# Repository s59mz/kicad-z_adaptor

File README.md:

# z_adaptor
Adaptor from Z-Turn I/O Expansion card to several Alinx DAC/ADC, HDMI, Ethernet modules and PMODS

Schematic:
[z_adaptor.pdf](z_adaptor.pdf)

BOM:
[z_adaptor.csv](z_adaptor.csv)

Gerbers:
[gerbers.zip](https://github.com/s59mz/kicad-z_adaptor/raw/main/gerbers.zip)

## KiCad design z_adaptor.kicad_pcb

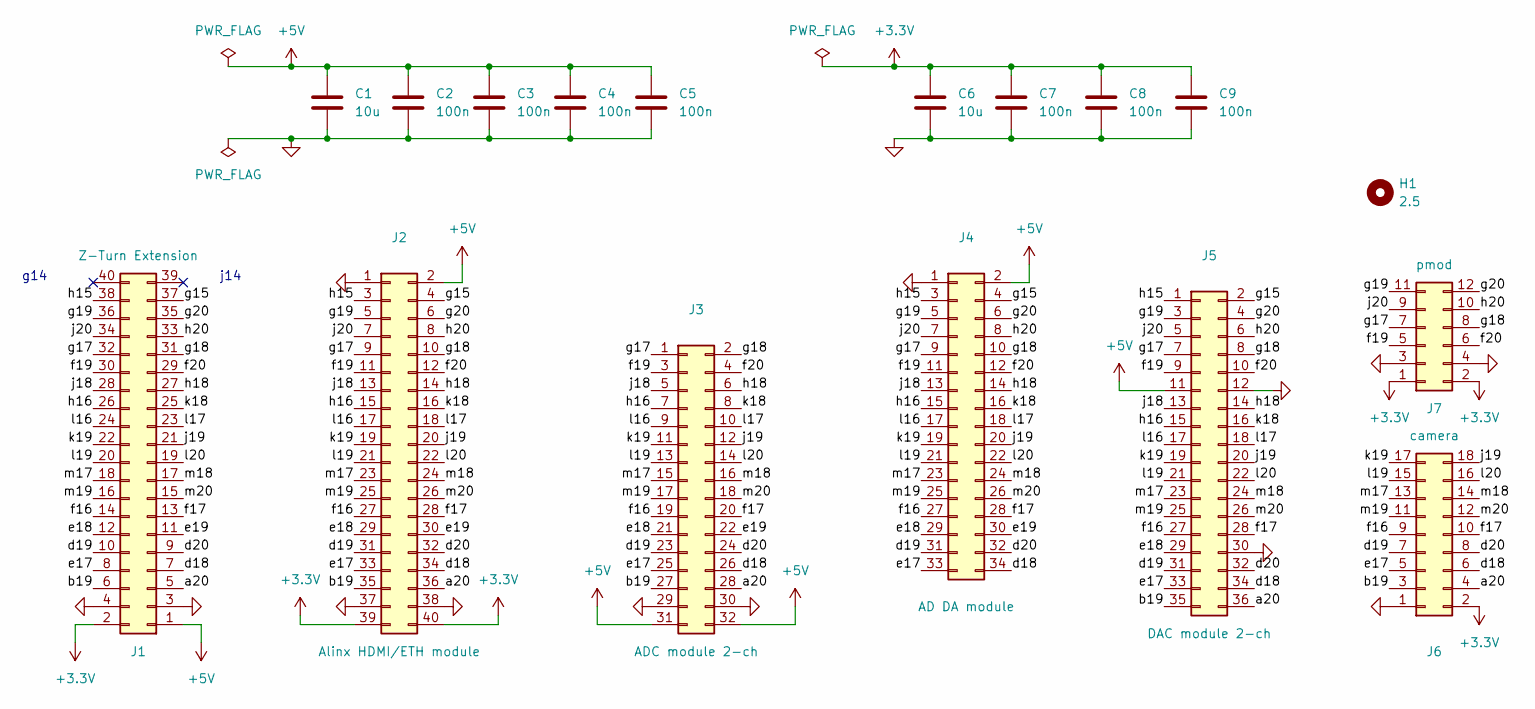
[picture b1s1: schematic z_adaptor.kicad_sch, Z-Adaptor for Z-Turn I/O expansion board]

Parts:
C1, C6: 10u; C_0603_1608Metric_Pad1.08x0.95mm_HandSolder
C2, C3, C4, C5, C7, C8, C9: 100n; C_0603_1608Metric_Pad1.08x0.95mm_HandSolder
H1: 2.5; MountingHole_2.5mm
J1: Z-Turn Extension; PinSocket_2x20_P2.54mm_Vertical
J2: Alinx HDMI/ETH module; PinHeader_2x20_P2.54mm_Vertical
J3: ADC module 2-ch; PinHeader_2x16_P2.54mm_Vertical
J4: AD DA module; PinHeader_2x17_P2.54mm_Vertical
J5: DAC module 2-ch; PinHeader_2x18_P2.54mm_Vertical
J6: camera; PinSocket_2x09_P2.54mm_Horizontal
J7: pmod; PinSocket_2x06_P2.54mm_Horizontal

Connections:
+3.3V: C6.1, C7.1, C8.1, C9.1, J1.2, J2.39, J2.40, J6.2, J7.1, J7.2
+5V: C1.1, C2.1, C3.1, C4.1, C5.1, J1.1, J2.2, J3.31, J3.32, J4.2, J5.11
/a20: J1.5, J2.36, J3.28, J5.36, J6.4
/b19: J1.6, J2.35, J3.27, J5.35, J6.3
/d18: J1.7, J2.34, J3.26, J4.34, J5.34, J6.6
/d19: J1.10, J2.31, J3.23, J4.31, J5.31, J6.7
/d20: J1.9, J2.32, J3.24, J4.32, J5.32, J6.8
/e17: J1.8, J2.33, J3.25, J4.33, J5.33, J6.5
/e18: J1.12, J2.29, J3.21, J4.29, J5.29
/e19: J1.11, J2.30, J3.22, J4.30
/f16: J1.14, J2.27, J3.19, J4.27, J5.27, J6.9
/f17: J1.13, J2.28, J3.20, J4.28, J5.28, J6.10
/f19: J1.30, J2.11, J3.3, J4.11, J5.9, J7.5
/f20: J1.29, J2.12, J3.4, J4.12, J5.10, J7.6
/g15: J1.37, J2.4, J4.4, J5.2
/g17: J1.32, J2.9, J3.1, J4.9, J5.7, J7.7
/g18: J1.31, J2.10, J3.2, J4.10, J5.8, J7.8
/g19: J1.36, J2.5, J4.5, J5.3, J7.11
/g20: J1.35, J2.6, J4.6, J5.4, J7.12
/h15: J1.38, J2.3, J4.3, J5.1
/h16: J1.26, J2.15, J3.7, J4.15, J5.15
/h18: J1.27, J2.14, J3.6, J4.14, J5.14
/h20: J1.33, J2.8, J4.8, J5.6, J7.10
/j18: J1.28, J2.13, J3.5, J4.13, J5.13
/j19: J1.21, J2.20, J3.12, J4.20, J5.20, J6.18
/j20: J1.34, J2.7, J4.7, J5.5, J7.9
/k18: J1.25, J2.16, J3.8, J4.16, J5.16
/k19: J1.22, J2.19, J3.11, J4.19, J5.19, J6.17
/l16: J1.24, J2.17, J3.9, J4.17, J5.17
/l17: J1.23, J2.18, J3.10, J4.18, J5.18
/l19: J1.20, J2.21, J3.13, J4.21, J5.21, J6.15
/l20: J1.19, J2.22, J3.14, J4.22, J5.22, J6.16
/m17: J1.18, J2.23, J3.15, J4.23, J5.23, J6.13
/m18: J1.17, J2.24, J3.16, J4.24, J5.24, J6.14
/m19: J1.16, J2.25, J3.17, J4.25, J5.25, J6.11
/m20: J1.15, J2.26, J3.18, J4.26, J5.26, J6.12
GND: C1.2, C2.2, C3.2, C4.2, C5.2, C6.2, C7.2, C8.2, C9.2, J1.3, J1.4, J2.1, J2.37, J2.38, J3.29, J3.30, J4.1, J5.12, J5.30, J6.1, J7.3, J7.4

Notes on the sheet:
j14
g14

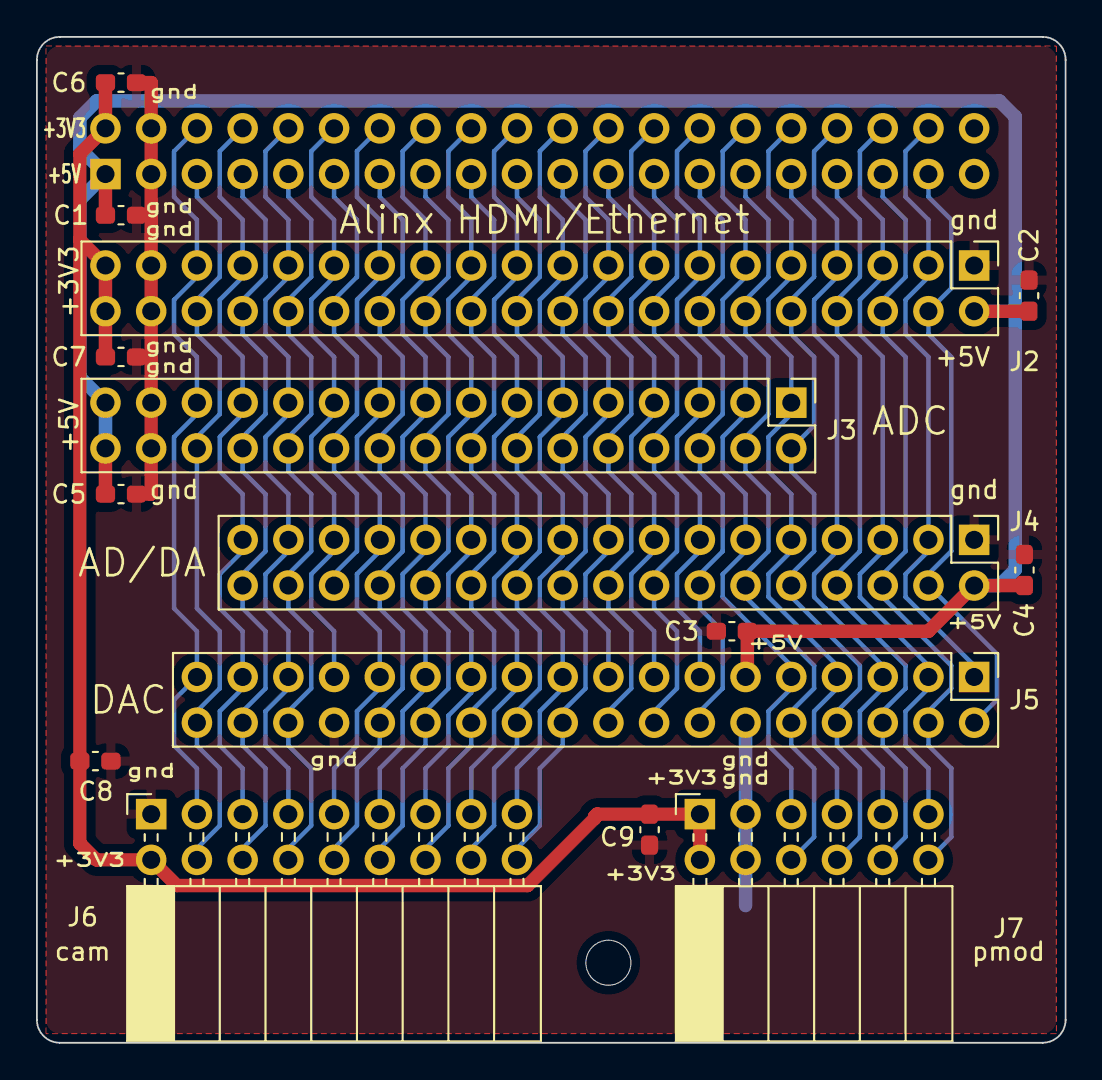
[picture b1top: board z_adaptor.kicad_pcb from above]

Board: 2 copper layers, 57.1 x 55.9 mm, 17 parts (1 on the bottom side), 37 nets.

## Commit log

2024-08-11 add screenshots
